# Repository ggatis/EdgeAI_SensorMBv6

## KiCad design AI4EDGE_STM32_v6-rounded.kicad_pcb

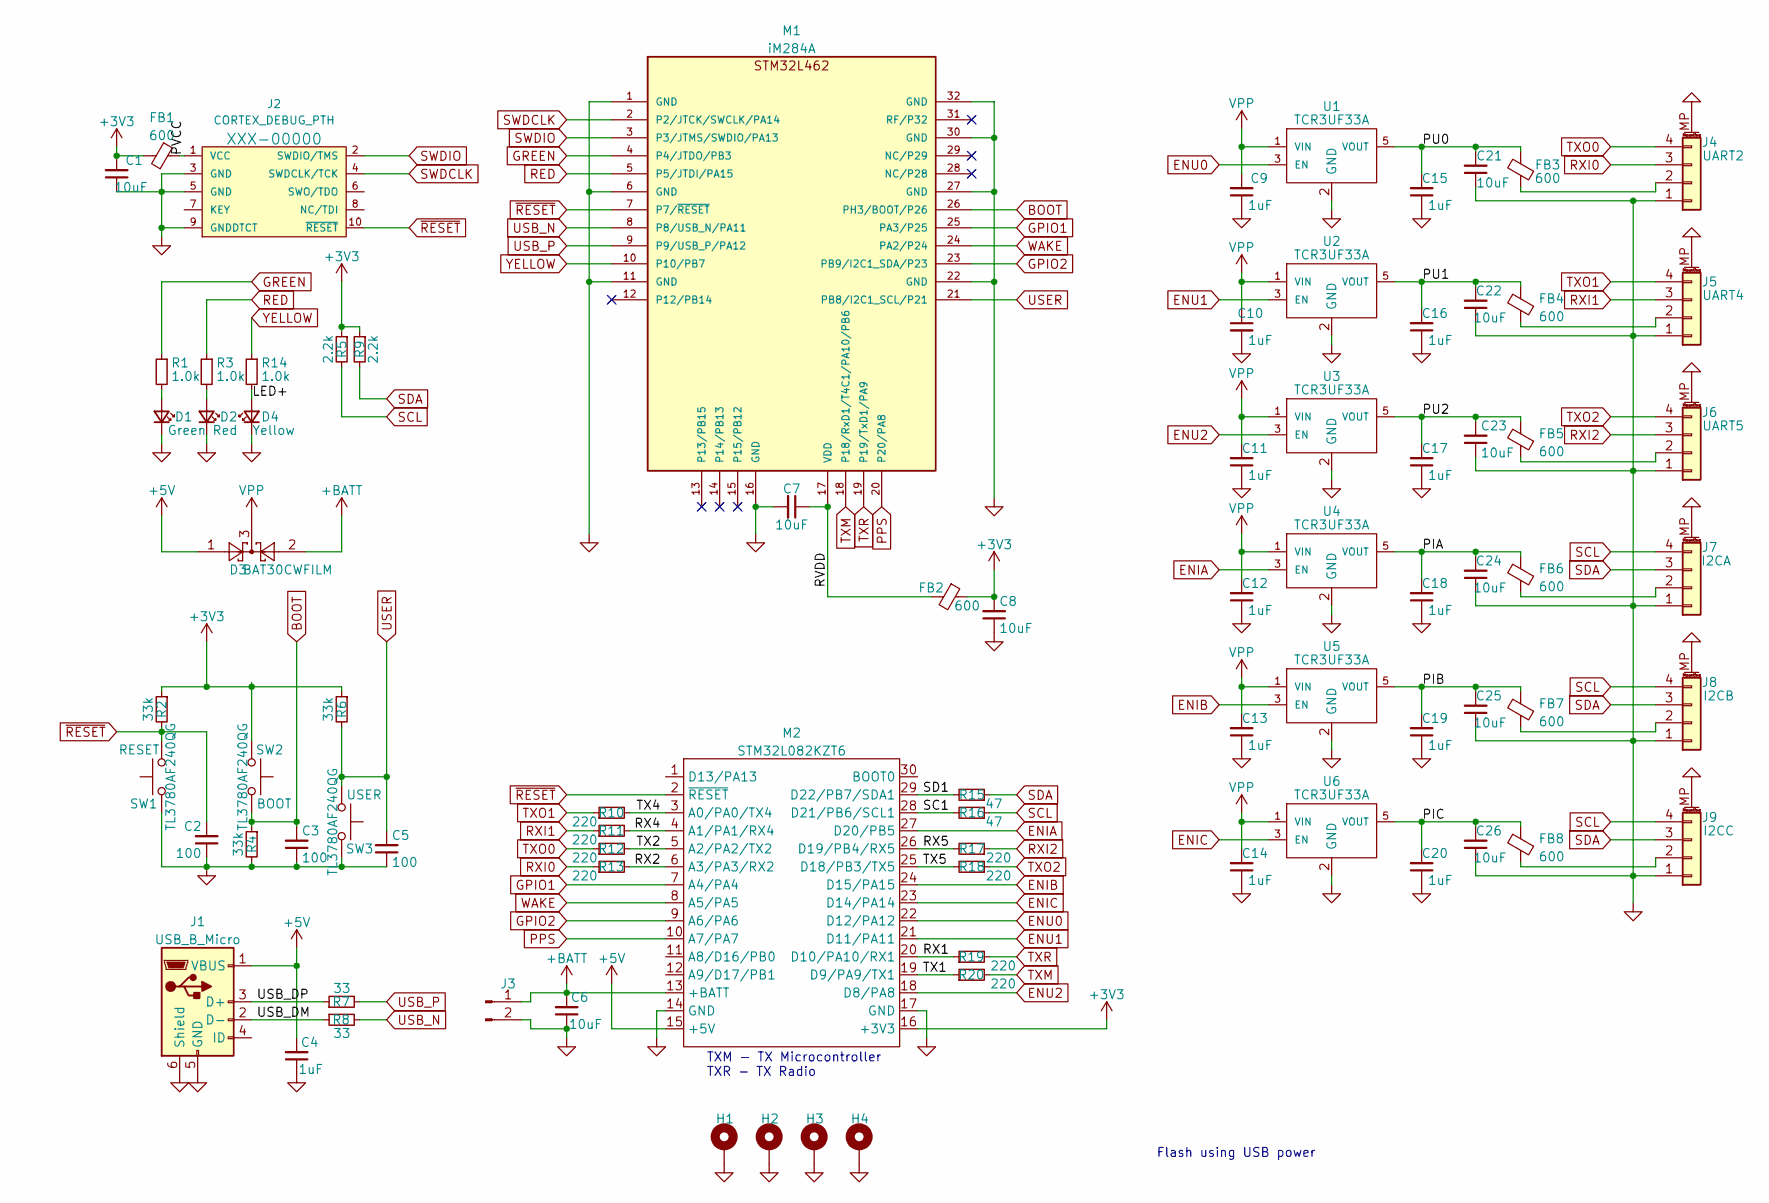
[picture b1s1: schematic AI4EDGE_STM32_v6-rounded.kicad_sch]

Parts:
C1, C6, C7, C8, C21, C22, C23, C24, C25, C26: 10uF; C_0603_1608Metric; MPN GRM188C80J106MEA6J
C2, C3, C5: 100; C_0603_1608Metric; MPN CC0603JRNPO9BN101
C4, C9, C10, C11, C12, C13, C14, C15, C16, C17, C18, C19, C20: 1uF; C_0402_1005Metric; MPN CL05X105KQ5NNNC
D1: Green; LED_0603_1608Metric; MPN LT Q99G.01-R2T1-25-1
D2: Red; LED_0603_1608Metric; MPN QBLP661-R5
D3: BAT30CWFILM; SOT-323_SC-70; MPN BAT30CWFILM
D4: Yellow; LED_0603_1608Metric; MPN QBLP601-Y5-2897
FB1, FB2, FB3, FB4, FB5, FB6, FB7, FB8: 600; Ferrite_0603_1608Metric; MPN MH1608-601Y
H1, H2, H3, H4: MountingHole_2.7mm_M2.5_DIN965_Pad; MountingHole_2.5mm_Pad_Via
J1: USB_B_Micro; USB_Micro-B_Wuerth_629105150521_CircularHoles; MPN 629105150521
J2: CORTEX_DEBUG_PTH; 2X5-PTH-1.27MM; MPN GRPB052VWVN-RC
J3: Battery; JST_EH_B2B-EH-A_1x02_P2.50mm_Vertical; MPN B2B-XH-A-GU
J4: UART2; JST_GH_BM04B-GHS-TBT_1x04-1MP_P1.25mm_Vertical; MPN BM04B-GHS-TBT
J5: UART4; JST_GH_BM04B-GHS-TBT_1x04-1MP_P1.25mm_Vertical; MPN BM04B-GHS-TBT
J6: UART5; JST_GH_BM04B-GHS-TBT_1x04-1MP_P1.25mm_Vertical; MPN BM04B-GHS-TBT
J7: I2CA; JST_GH_BM04B-GHS-TBT_1x04-1MP_P1.25mm_Vertical; MPN BM04B-GHS-TBT
J8: I2CB; JST_GH_BM04B-GHS-TBT_1x04-1MP_P1.25mm_Vertical; MPN BM04B-GHS-TBT
J9: I2CC; JST_GH_BM04B-GHS-TBT_1x04-1MP_P1.25mm_Vertical; MPN BM04B-GHS-TBT
M1: iM284A
M2: STM32L082KZT6; STM32L082KZT6_pink_pill; MPN ICM-632-1-GT-HT
R1, R3, R14: 1.0k; R_0603_1608Metric
R2, R4, R6: 33k; R_0603_1608Metric
R5, R9: 2.2k; R_0603_1608Metric; MPN WR06X222 JTL
R7: 33; R_0402_1005Metric; MPN PFR05S-100-FNH
R8: 33; R_0402_1005Metric
R10, R11, R12, R13, R17, R18, R19, R20: 220; R_0603_1608Metric; MPN WR06X221 JTL
R15, R16: 47; R_0603_1608Metric
SW1, SW2, SW3: TL3780AF240QG; SW_TL3780AF240QG; MPN TL3780AF240QG
U1, U2, U3, U4, U5, U6: TCR3UF33A; SOT-25; MPN TCR3UF33A

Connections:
+3V3: C1.2, C8.2, FB1.2, FB2.1, M2.16 (+3V3), R2.1, R5.1, R6.1, R9.1, SW2.2
+5V: C4.2, D3.1, J1.1 (VBUS), M2.15 (+5V)
+BATT: C6.2, D3.2, J3.1, M2.13 (+BATT)
/LED+: D4.2 (A), R14.2
/PIA: C18.2, C24.2, FB6.2, U4.5 (VOUT)
/PIB: C19.2, C25.2, FB7.2, U5.5 (VOUT)
/PIC: C20.2, C26.2, FB8.2, U6.5 (VOUT)
/PU0: C15.2, C21.2, FB3.2, U1.5 (VOUT)
/PU1: C16.2, C22.2, FB4.2, U2.5 (VOUT)
/PU2: C17.2, C23.2, FB5.2, U3.5 (VOUT)
/PVCC: FB1.1, J2.1 (VCC)
/RVDD: C7.1, FB2.2, M1.17 (VDD)
/RX1: M2.20 (D10/PA10/RX1), R19.1
/RX2: M2.6 (A3/PA3/RX2), R13.2
/RX4: M2.4 (A1/PA1/RX4), R11.2
/RX5: M2.26 (D19/PB4/RX5), R17.2
/SC1: M2.28 (D21/PB6/SCL1), R16.2
/SD1: M2.29 (D22/PB7/SDA1), R15.2
/TX1: M2.19 (D9/PA9/TX1), R20.1
/TX2: M2.5 (A2/PA2/TX2), R12.2
/TX4: M2.3 (A0/PA0/TX4), R10.2
/TX5: M2.25 (D18/PB3/TX5), R18.2
/USB_DM: J1.2 (D-), R8.1
/USB_DP: J1.3 (D+), R7.1
BOOT: C3.2, M1.26 (PH3/BOOT/P26), R4.1, SW2.1
ENIA: M2.27 (D20/PB5), U4.3 (EN)
ENIB: M2.24 (D15/PA15), U5.3 (EN)
ENIC: M2.23 (D14/PA14), U6.3 (EN)
ENU0: M2.22 (D12/PA12), U1.3 (EN)
ENU1: M2.21 (D11/PA11), U2.3 (EN)
ENU2: M2.18 (D8/PA8), U3.3 (EN)
GND: C1.1, C2.1, C3.1, C4.1, C5.1, C6.1, C7.2, C8.1, C9.1, C10.2, C11.1, C12.1, C13.1, C14.1, C15.1, C16.1, C17.1, C18.1, C19.1, C20.1, C21.1, C22.1, C23.1, C24.1, C25.1, C26.1, D1.1 (K), D2.1 (K), D4.1 (K), H1.1, H2.1, H3.1, H4.1, J1.5 (GND), J1.6 (Shield), J2.3 (GND), J2.5 (GND), J2.9 (GNDDTCT), J3.2, J4.1, J4.MP (MountPin), J5.1, J5.MP (MountPin), J6.1, J6.MP (MountPin), J7.1, J7.MP (MountPin), J8.1, J8.MP (MountPin), J9.1, J9.MP (MountPin), M1.1 (GND), M1.6 (GND), M1.11 (GND), M1.16 (GND), M1.22 (GND), M1.27 (GND), M1.30 (GND), M1.32 (GND), M2.14 (GND), M2.17 (GND), R4.2, SW1.2, SW3.2, U1.2 (GND), U2.2 (GND), U3.2 (GND), U4.2 (GND), U5.2 (GND), U6.2 (GND)
GPIO1: M1.25 (PA3/P25), M2.7 (A4/PA4)
GPIO2: M1.23 (PB9/I2C1_SDA/P23), M2.9 (A6/PA6)
GREEN: M1.4 (P4/JTDO/PB3), R1.1
unnamed: D1.2 (A), R1.2
unnamed: D2.2 (A), R3.2
unnamed: FB3.1, J4.2
unnamed: FB4.1, J5.2
unnamed: FB5.1, J6.2
unnamed: FB6.1, J7.2
unnamed: FB7.1, J8.2
unnamed: FB8.1, J9.2
PPS: M1.20 (P20/PA8), M2.10 (A7/PA7)
RED: M1.5 (P5/JTDI/PA15), R3.1
RXI0: J4.3, R13.1
RXI1: J5.3, R11.1
RXI2: J6.3, R17.1
SCL: J7.4, J8.4, J9.4, R5.2, R16.1
SDA: J7.3, J8.3, J9.3, R9.2, R15.1
SWDCLK: J2.4 (SWDCLK/TCK), M1.2 (P2/JTCK/SWCLK/PA14)
SWDIO: J2.2 (SWDIO/TMS), M1.3 (P3/JTMS/SWDIO/PA13)
TXM: M1.18 (P18/RxD1/T4C1/PA10/PB6), R20.2
TXO0: J4.4, R12.1
TXO1: J5.4, R10.1
TXO2: J6.4, R18.1
TXR: M1.19 (P19/TxD1/PA9), R19.2
USB_N: M1.8 (P8/USB_N/PA11), R8.2
USB_P: M1.9 (P9/USB_P/PA12), R7.2
USER: C5.2, M1.21 (PB8/I2C1_SCL/P21), R6.2, SW3.1
VPP: C9.2, C10.1, C11.2, C12.2, C13.2, C14.2, D3.3, U1.1 (VIN), U2.1 (VIN), U3.1 (VIN), U4.1 (VIN), U5.1 (VIN), U6.1 (VIN)
WAKE: M1.24 (PA2/P24), M2.8 (A5/PA5)
YELLOW: M1.10 (P10/PB7), R14.1
~RESET: C2.2, J2.10 (~RESET), M1.7 (P7/~RESET), M2.2 (~RESET), R2.2, SW1.1

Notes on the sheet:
Flash using USB power
TXM - TX Microcontroller TXR - TX Radio

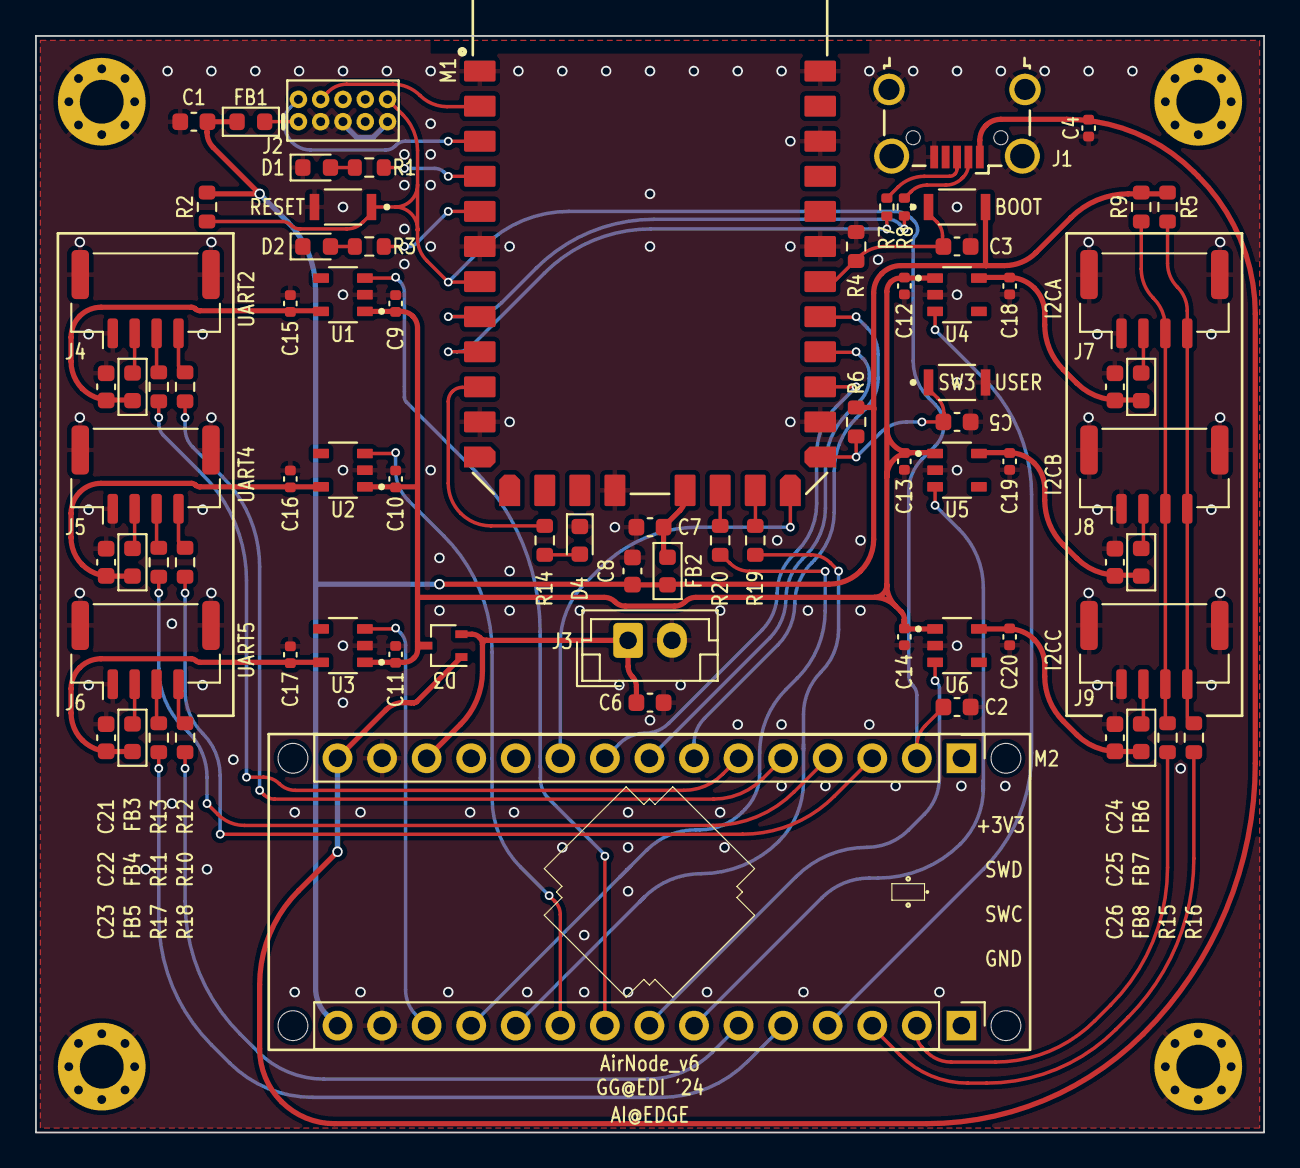
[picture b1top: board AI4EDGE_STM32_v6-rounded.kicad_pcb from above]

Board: 2 copper layers, 70.0 x 62.5 mm, 82 parts (0 on the bottom side), 64 nets.
